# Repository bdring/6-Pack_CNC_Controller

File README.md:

# 6-Pack Grbl_ESP32 CNC Controller

### Overview

This is a fully modular CNC controller that runs Grbl_ESP32 firmware.

### Current Source Files.

The latest versions are [now on OSHLabs](https://oshwlab.com/bdring?tab=project&page=1) with the free version of EasyEDA. I did this to make it more accessible and easier to order.

### Features

- ESP32 Sockets to fit both narrow and wide 2 x 19 pin types.
- (6) Stepper Driver Outputs. These can be used for 6 axes (XYZABC) or any (2) can be ganged to allow dual motors on a single axis. These ganged motors can be controlled independently for axis squaring. It supports these types of drivers. Each driver has an independent enable/disable pin.
  - Standard Pololu/StepStick style driver modules.
  - Trinamic SPI type drivers. These are the ultra quiet types with sensorless endstop capability.
  - External Driver with 5V opto isolators.
(5) CNC I/O Modules. These interface with your machine. They include, but are not limited to, siwtch inputs, spindle control and accessory control. Currently there are (5) modules available.
  - High current AC/DC relay
  - 4x 5V Buffered output for lasers, PWM, spindle direction, spindle enable, ect.
  - RS485 Modbus Spindles
  - 0-10V Output Spindles
  - 4x Switch input with Optocouplers, filtering and Schmitt triggers. 
- SD Card Socket
- JTAG Programming/Debugging connector (or access to addition I/O pins

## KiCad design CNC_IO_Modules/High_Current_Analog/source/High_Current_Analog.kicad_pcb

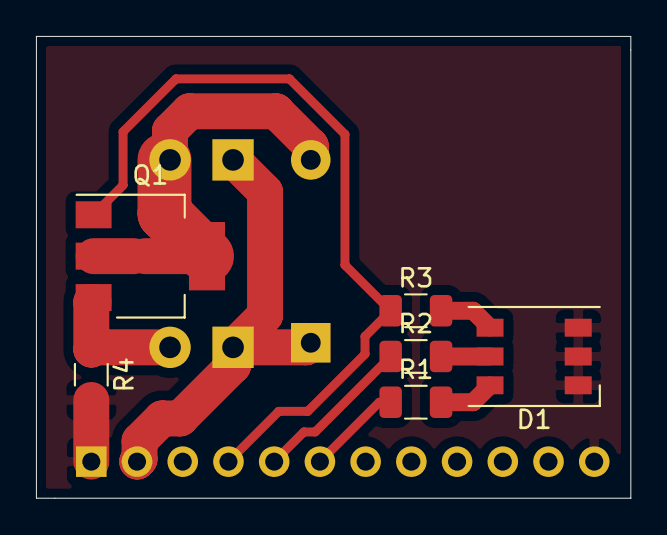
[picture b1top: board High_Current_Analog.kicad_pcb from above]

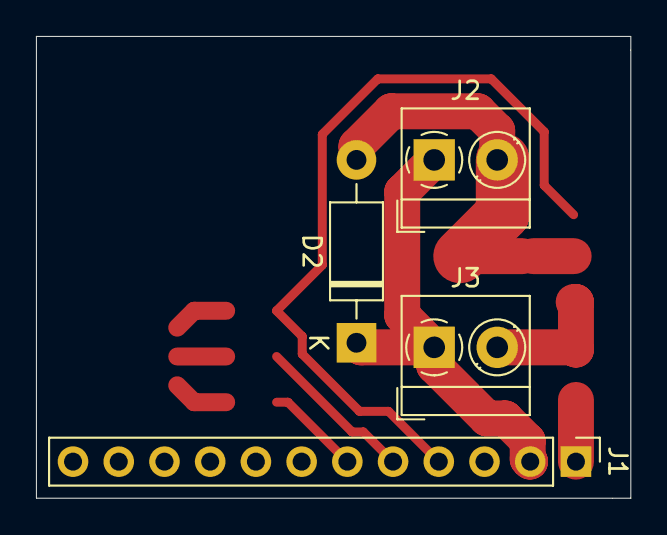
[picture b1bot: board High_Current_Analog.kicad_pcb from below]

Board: 2 copper layers, 33.0 x 25.7 mm, 10 parts (4 on the bottom side), 10 nets.

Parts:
D1: LED_RGB; LED_WS2812_PLCC6_5.0x5.0mm_P1.6mm
D2: 1N4003; D_DO-41_SOD81_P10.16mm_Horizontal
J1: Conn_01x12_Male; PinHeader_1x12_P2.54mm_Vertical
J2, J3: Screw_Terminal_01x02; TerminalBlock_MetzConnect_Type059_RT06302HBWC_1x02_P3.50mm_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
Q1: Q_NMOS_GDSD; SOT-223
R1, R2, R3, R4: R; R_1206_3216Metric

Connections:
GND: D1.1, D1.2, D1.3, J1.1, J1.12, R4.2
GNDPWR: J3.2, Q1.3, R4.1
IN1: J1.4, Q1.1, R3.1
IN2: J1.5, R2.1
IN3: J1.6, R1.1
unnamed: D1.4, R3.2
unnamed: D1.5, R2.2
unnamed: D1.6, R1.2
OUT1: D2.2, J2.2, Q1.2, Q1.4
VCC: D2.1, J1.2, J2.1, J3.1

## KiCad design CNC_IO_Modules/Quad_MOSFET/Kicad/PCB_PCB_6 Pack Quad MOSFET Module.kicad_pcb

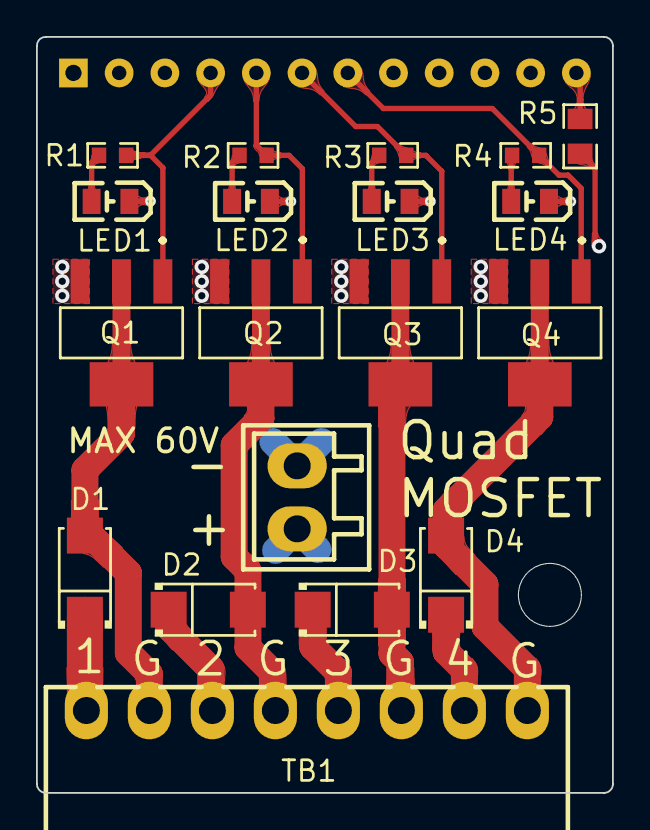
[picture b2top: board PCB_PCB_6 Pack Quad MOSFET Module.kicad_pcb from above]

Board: 2 copper layers, 32.0 x 42.0 mm, 20 parts (0 on the bottom side), 15 nets.

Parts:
D1, D2, D3, D4: B340A; SMA_L4.3-W2.6-LS5.2-RD
LED1, LED2, LED3, LED4: SZYY0805G; LED0805-R-RD
MOD1: 6 Pack Module Pins Bottom; 6 PACK MODULE PCB BOTTOM
Q1, Q2, Q3, Q4: NCE6005AR; SOT-223_L6.5-W3.5-P2.30-LS7.0-BR
R1, R2, R3, R4: 5.1kΩ; R0603
R5: 10MΩ; R0805
TB1: KF2EDGR-3.5-8P; CONN-TH_8P-P3.50_KF2EDGR-3.5-8P
TB2: KF2EDGV-3.5-2P; CONN-TH_P3.50_KF2EDGV-3.5-2P

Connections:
GND: LED1.2, LED2.2, LED3.2, LED4.2, MOD1.1, MOD1.12, R5.1
GND_VM: Q1.3, Q2.3, Q3.3, Q4.3, R5.2, TB2.2
LED1_1: LED1.1, R1.1
LED2_1: LED2.1, R2.1
LED3_1: LED3.1, R3.1
LED4_1: LED4.1, R4.1
MOD1_4: MOD1.4, Q1.1, R1.2
MOD1_5: MOD1.5, Q2.1, R2.2
MOD1_6: MOD1.6, Q3.1, R3.2
MOD1_7: MOD1.7, Q4.1, R4.2
Q1_2: D1.2, Q1.2, Q1.4, TB1.2
Q2_2: D2.2, Q2.2, Q2.4, TB1.4
Q3_2: D3.2, Q3.2, Q3.4, TB1.6
Q4_2: D4.2, Q4.2, Q4.4, TB1.8
VM: D1.1, D2.1, D3.1, D4.1, TB1.1, TB1.3, TB1.5, TB1.7, TB2.1

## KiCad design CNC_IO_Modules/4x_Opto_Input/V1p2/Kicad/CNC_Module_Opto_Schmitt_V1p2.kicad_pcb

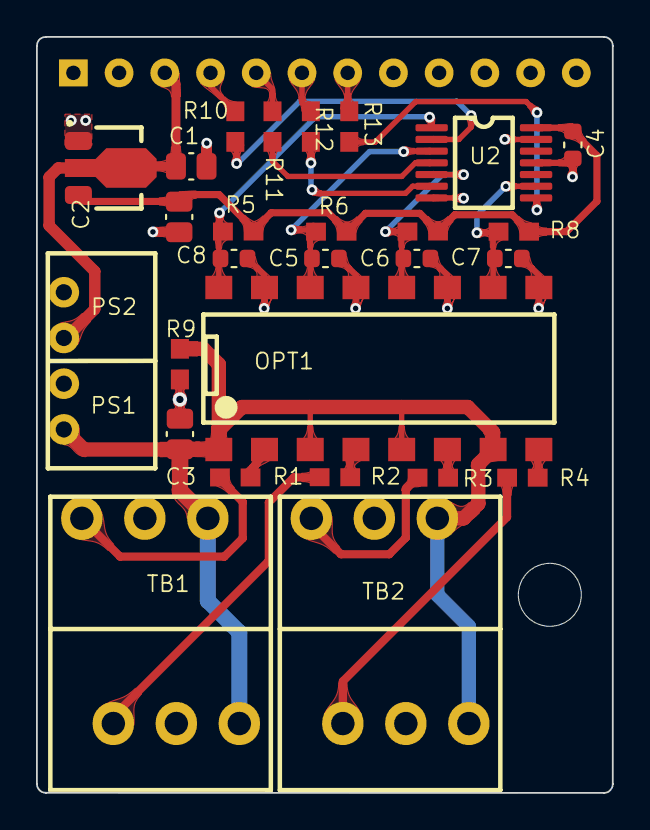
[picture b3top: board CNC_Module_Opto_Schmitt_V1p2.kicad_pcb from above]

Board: 2 copper layers, 32.0 x 42.0 mm, 28 parts (0 on the bottom side), 25 nets.

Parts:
C1, C2: 1uF; CAP_0805_N
C3: 2.2uF; CAP_0805_N_C3
C4: 100nF; CAP_0603_N
C5, C6, C7, C8: 100nF; CAP_0603_N_C5
MOD1: CNC_MODULE; CNC_Module_V3
OPT1: TP521-4; TLP521-4SM
PS1: 5V; B0505S-1WR3
PS2: 3.3V; SOT89
R1, R2, R3: 300R; RES_0603
R4: 300R; RES_0603_R4
R5: 10k; RES_0603_R5
R6: 10k; RES_0603_R6
R7: 10k; RES_0603_R7
R8: 10k; RES_0603_R8
R9: 220R; RES_0603_R9
R10: 220R; RES_0603_R10
R11: 220R; RES_0603
R12, R13: 220R; RES_0603_R12
TB1, TB2: KL128H-3.5_3X2; KF128-3.5-3x2
U2: SN74AC14D; TSSOP-14

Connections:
3v3: C2.1, C4.1, PS2.3, R5.1, R6.1, R7.1, R8.1, U2.14
5V: C1.1, MOD1.3, PS1.2, PS2.2
Gnd: C1.2, C2.2, C4.2, C5.1, C6.1, C7.1, C8.1, MOD1.1, MOD1.12, OPT1.9, OPT1.11, OPT1.13, OPT1.15, PS1.1, PS2.1, U2.7, U2.11, U2.13
Net_2: C3.1, OPT1.1, OPT1.3, OPT1.5, OPT1.7, PS1.4, R9.2, TB1.3, TB1.6, TB2.3, TB2.6
Net_3: OPT1.2, R1.2
Net_4: OPT1.4, R2.2
Net_5: OPT1.6, R3.2
Net_6: OPT1.8, R4.2
Net_8: C8.2, OPT1.16, R5.2, U2.1
Net_9: C5.2, OPT1.14, R6.2, U2.3
Net_11: C6.2, OPT1.12, R7.2, U2.5
Net_12: C7.2, OPT1.10, R8.2, U2.9
Net_13: R1.1, TB1.1
Net_14: R2.1, TB1.4
Net_15: R3.1, TB2.1
Net_16: R4.1, TB2.4
Net_17: MOD1.7, R13.1
Net_18: MOD1.4, R10.1
Net_19: MOD1.5, R11.1
Net_20: MOD1.6, R12.1
Net_21: R10.2, U2.2
Net_22: R11.2, U2.4
Net_23: R13.2, U2.8
Net_24: R12.2, U2.6
Net_31: C3.2, PS1.3, R9.1, TB1.2, TB1.5, TB2.2, TB2.5

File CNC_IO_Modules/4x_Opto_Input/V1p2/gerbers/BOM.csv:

"RefDes","Value","Name","Quantity","Manufacturer","MFG P/N"
"C1, C2","1uF","NP_1uF_50V_0805","2","CCTC","TCC0805X7R105K500DTB"
"C3","2.2uF","NP_2.2uF_16V_0805","1","Samsung Electro-Mechanics","CL21B225KOFNNNE"
"C4, C5, C6, C7, C8","100nF","NP_100nF_50V_0603","5","KEMET","C0603C104K5RACTU"
"MOD1","","CNC_Module","1","CJT(Changjiang Connectors)","A2541WV-12P"
"OPT1","TP521-4","TLP521-4","1","Isocom Components","TLP521-4GBSM"
"PS1","5V","B0505S-1WR3","1","MORNSUN Guangzhou S&T","B0505S-1WR3"
"PS2","3.3V","LDO_3V3_150mA_SOT-89","1","Diodes Incorporated","AP2204RA-3.3TRG1"
"R1, R2, R3, R4","300R","300R_0603","4","YAGEO","RC0603FR-07330RL"
"R5, R6, R7, R8","10k","10k_0603","4","YAGEO","RC0603FR-0710KL"
"R9, R10, R11, R12, R13","220R","220R_0603","5","YAGEO","RC0603FR-07220RL"
"TB1, TB2","","KL128H-3.5_3x2","2","KEFA","KF128A-3.5 3P"
"U2","","SN74AC14D","1","Texas Instruments","SN74HC14PWR"

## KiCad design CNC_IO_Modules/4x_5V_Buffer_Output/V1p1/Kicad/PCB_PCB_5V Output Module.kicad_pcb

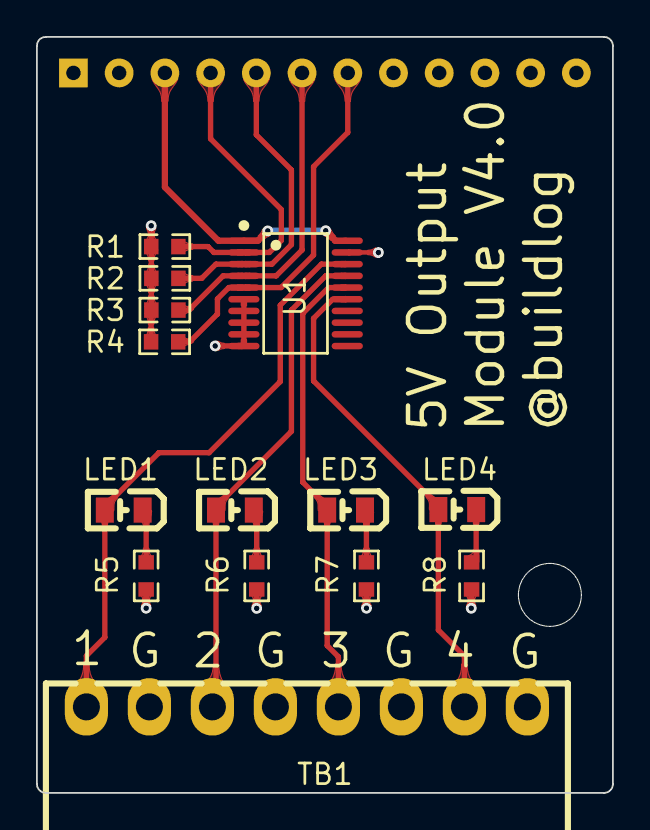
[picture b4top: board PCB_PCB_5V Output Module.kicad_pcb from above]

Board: 2 copper layers, 32.0 x 42.0 mm, 15 parts (0 on the bottom side), 14 nets.

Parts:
LED1, LED2, LED3, LED4: SZYY0805G; LED0805-R-RD
MOD1: 6 Pack Module Pins Bottom 3D; 6 PACK MODULE PCB BOTTOM_3D
R1, R2, R3, R4: 10kΩ; R0603
R5, R6, R7, R8: 5.1kΩ; R0603
TB1: KF2EDGR-3.5-8P; CONN-TH_8P-P3.50_KF2EDGR-3.5-8P
U1: MC74ACT245DTR2G; TSSOP-20_L6.5-W4.4-P0.65-LS6.4-BL

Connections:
+5V: MOD1.3, U1.1, U1.20
GND: MOD1.1, MOD1.12, R1.1, R2.1, R3.1, R4.1, R5.1, R6.1, R7.2, R8.2, TB1.2, TB1.4, TB1.6, TB1.8, U1.6, U1.7, U1.8, U1.9, U1.10, U1.19
LED1_2: LED1.2, R5.2
LED2_2: LED2.2, R6.2
LED3_2: LED3.2, R7.1
LED4_2: LED4.2, R8.1
OUT1: MOD1.4, R1.2, U1.2
OUT2: MOD1.5, R2.2, U1.3
OUT3: MOD1.6, R3.2, U1.4
OUT4: MOD1.7, R4.2, U1.5
U1_15: LED4.1, TB1.7, U1.15
U1_16: LED3.1, TB1.5, U1.16
U1_17: LED2.1, TB1.3, U1.17
U1_18: LED1.1, TB1.1, U1.18

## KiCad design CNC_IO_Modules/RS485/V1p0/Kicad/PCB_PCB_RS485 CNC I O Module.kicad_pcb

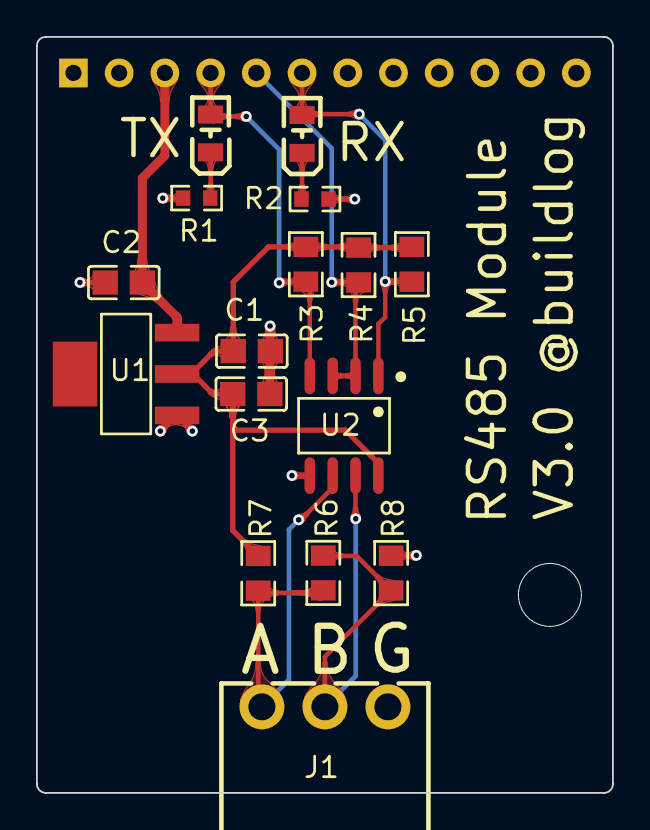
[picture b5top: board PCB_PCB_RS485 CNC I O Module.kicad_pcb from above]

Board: 2 copper layers, 32.0 x 42.0 mm, 17 parts (0 on the bottom side), 10 nets.

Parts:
C1, C2: 10uF; C0805
C3: 100nF; C0805
J1: KF2EDGR-3.5-3P; CONN-TH_3P-P3.50_KF2EDGR-3.5-3P
LED1, LED2: SZYY0805G; LED0805-R-RD
MOD1: 6 Pack Module Pins Bottom; 6 PACK MODULE PCB BOTTOM
R1, R2: 2kΩ; R0603
R3, R4, R5: 10kΩ; R0805
R6: 120Ω; R0805
R7, R8: 20kΩ; R0805
U1: AMS1117-3.3_C369933; SOT-223-4_L6.5-W3.5-P2.30-LS7.0-BR
U2: MAX3485ESA+T; SOIC-8_L4.9-W3.9-P1.27-LS6.0-BL

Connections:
+3V3: C1.2, C3.2, R3.2, R4.2, R5.2, R7.2, U1.2, U2.8
+5V: C2.2, MOD1.3, U1.3
GND: C1.1, C2.1, C3.1, J1.3, MOD1.1, MOD1.12, R1.1, R2.1, R8.1, U1.1, U2.5
MOD_CTRL: MOD1.5, R4.1, U2.2, U2.3
MOD_RX: LED2.1, MOD1.6, R5.1, U2.1
MOD_TX: LED1.1, MOD1.4, R3.1, U2.4
R1_2: LED1.2, R1.2
R2_2: LED2.2, R2.2
U2_6: J1.1, R6.2, R7.1, U2.6
U2_7: J1.2, R6.1, R8.2, U2.7

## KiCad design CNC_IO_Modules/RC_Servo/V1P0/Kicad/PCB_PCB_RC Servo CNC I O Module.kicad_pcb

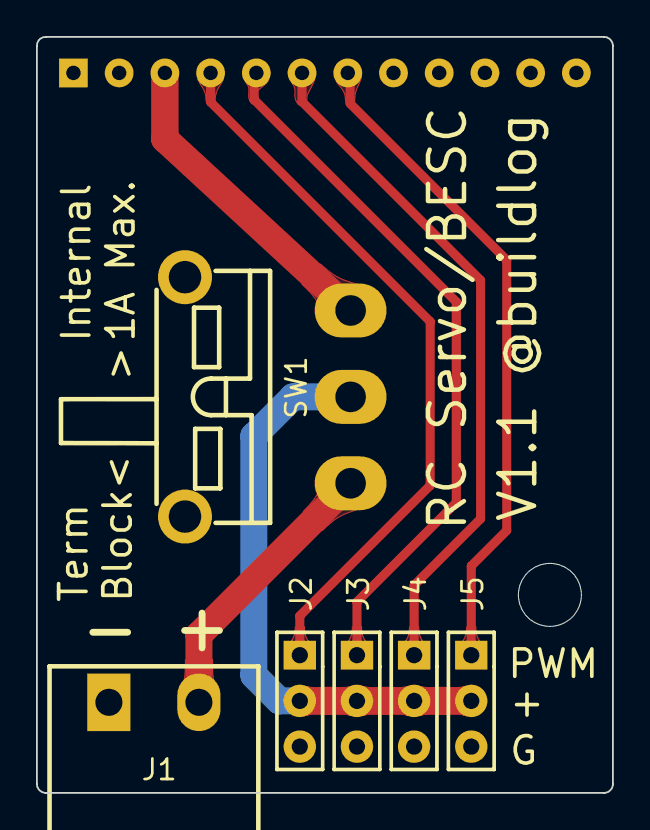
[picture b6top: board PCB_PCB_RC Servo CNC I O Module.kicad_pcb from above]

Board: 2 copper layers, 32.0 x 42.0 mm, 7 parts (0 on the bottom side), 8 nets.

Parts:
J1: XY2500R-B-5.00-2P; CONN-TH_2P-P5.00_XY2500R-B-5.00-2P
J2, J3, J4, J5: Header-Male-2.54_1x3; HDR-TH_3P-P2.54-V-M-1
MOD1: 6 Pack Module Pins Bottom; 6 PACK MODULE PCB BOTTOM
SW1: SS-12D11G5; SW-TH_SS-12D11G5

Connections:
+5V: MOD1.3, SW1.3
GND: J1.1, J2.3, J3.3, J4.3, J5.3, MOD1.1, MOD1.12
OUT1: J2.1, MOD1.4
OUT2: J3.1, MOD1.5
OUT3: J4.1, MOD1.6
OUT4: J5.1, MOD1.7
V_EXT: J1.2, SW1.1
V_SERVO: J2.2, J3.2, J4.2, J5.2, SW1.2

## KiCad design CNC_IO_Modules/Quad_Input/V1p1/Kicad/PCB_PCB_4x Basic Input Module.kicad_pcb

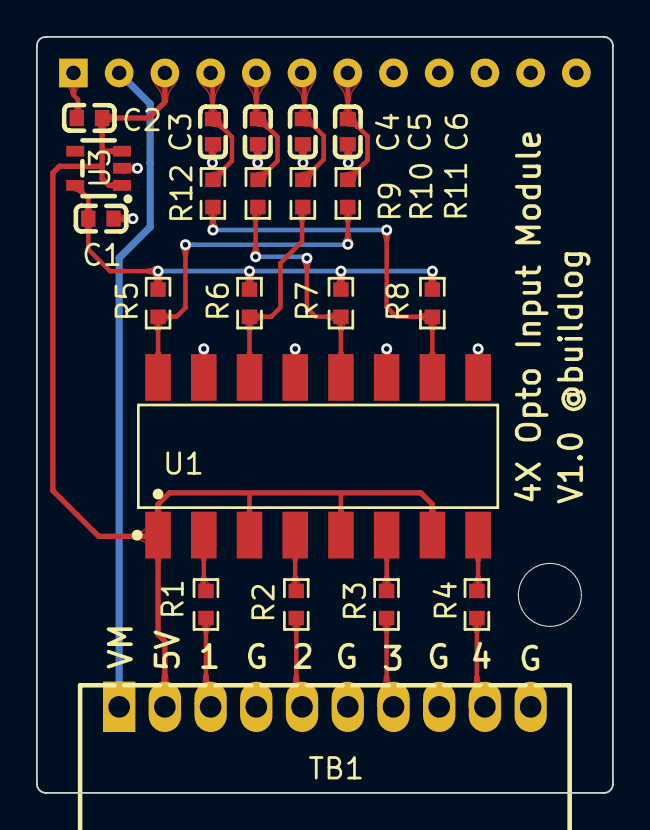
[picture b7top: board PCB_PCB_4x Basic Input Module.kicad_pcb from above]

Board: 2 copper layers, 32.0 x 42.0 mm, 22 parts (0 on the bottom side), 20 nets.

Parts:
C1, C2: 1uF; C0603
C3, C4, C5, C6: 100nF; C0603
MOD1: 6 Pack Module Pins Bottom 3D; 6 PACK MODULE PCB BOTTOM_3D
R1, R2, R3, R4: 300Ω; R0603
R5, R6, R7, R8: 10kΩ; R0603
R9, R10, R11, R12: 1kΩ; R0603
TB1: KF2EDGR-2.54-10P; CONN-TH_10P-P2.54_KF2EDGR-2.54-10P
U1: TLP521-4XSM; SMD-16_L20.0-W6.5-P2.54-LS10.2-BL
U3: LP5907MFX-3.3/NOPB; SOT-23-5_L3.0-W1.7-P0.95-LS2.8-BR

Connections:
+3V3: C1.2, R5.2, R6.2, R7.2, R8.2, U3.5
+5V: C2.2, MOD1.3, TB1.2, U1.1, U1.3, U1.5, U1.7, U3.1, U3.3
GND: C1.1, C2.1, C3.1, C4.1, C5.1, C6.1, MOD1.1, MOD1.12, TB1.4, TB1.6, TB1.8, TB1.10, U1.9, U1.11, U1.13, U1.15, U3.2
INPUT1: C6.2, MOD1.7, R11.2
INPUT2: C5.2, MOD1.6, R10.2
INPUT3: C4.2, MOD1.5, R9.2
INPUT4: C3.2, MOD1.4, R12.2
TB1_3: R1.1, TB1.3
TB1_5: R2.1, TB1.5
TB1_7: R3.1, TB1.7
TB1_9: R4.1, TB1.9
U1_2: R1.2, U1.2
U1_4: R2.2, U1.4
U1_6: R3.2, U1.6
U1_8: R4.2, U1.8
U1_10: R8.1, R12.1, U1.10
U1_12: R7.1, R9.1, U1.12
U1_14: R6.1, R10.1, U1.14
U1_16: R5.1, R11.1, U1.16
VMOT: MOD1.2, TB1.1

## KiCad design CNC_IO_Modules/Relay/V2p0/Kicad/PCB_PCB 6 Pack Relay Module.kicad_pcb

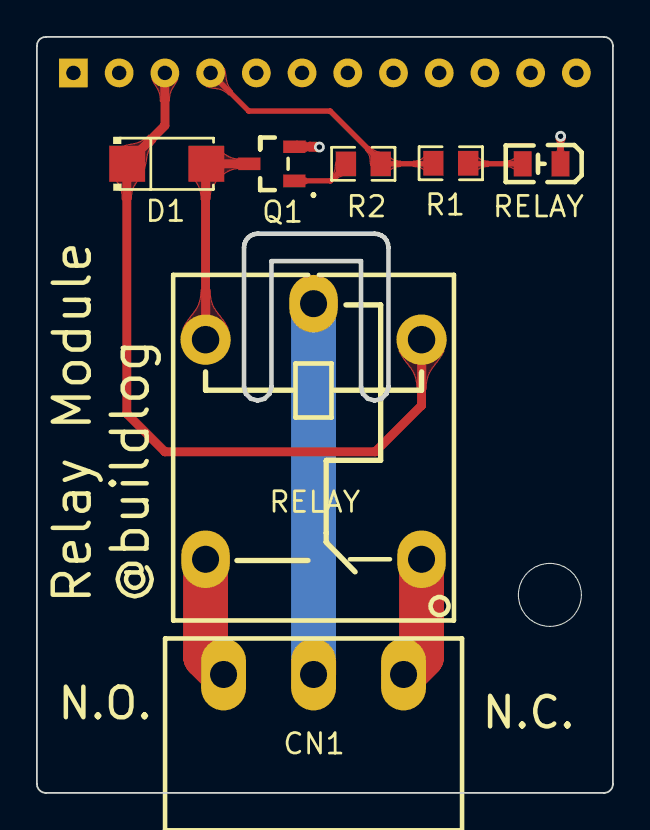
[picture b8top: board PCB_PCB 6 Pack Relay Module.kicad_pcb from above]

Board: 2 copper layers, 31.8 x 41.8 mm, 8 parts (0 on the bottom side), 9 nets.

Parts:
CN1: XY2500R-B-5.00-3P; CONN-TH_XY2500R-B-5.00-3P
D1: B340A; SMA_L4.3-W2.6-LS5.2-RD
MOD1: 6 Pack Module Pins Bottom 3D; 6 PACK MODULE PCB BOTTOM_3D
Q1: MMBT9014B; TO-236-3_L2.9-W1.3-P1.90-LS2.4-BR
R1: 2kΩ; R0805
R2: 1kΩ; R0805
RELAY: SZYY0805G; LED0805-R-RD
RELAY#2: SRD-05VDC-SL-C; RELAY-TH_SRD-XXVDC-XL-C

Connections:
+5V: D1.1, MOD1.3, RELAY#2.4
GND: MOD1.1, MOD1.12, Q1.2, RELAY.2
Q1_1: Q1.1, R2.2
R1_1: R1.1, RELAY.1
R2_1: MOD1.4, R1.2, R2.1
RLY1_1: D1.2, Q1.3, RELAY#2.1
RLY1_2: CN1.1, RELAY#2.2
RLY1_3: CN1.3, RELAY#2.3
RLY1_5: CN1.2, RELAY#2.5

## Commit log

2020-05-29 First Push
2020-05-29 Add photo
2020-06-27 Uploading V1p0
2020-06-27 moved schematic
2020-07-12 Added CNC I/O Modules
2020-07-12 Added image
2020-07-12 Add relay module image
2020-07-14 Added version 1p1
2020-07-15 Adding schemaic PDF
2020-07-25 Updating modules and adding external driver adapter
2020-08-07 Adding 3D files for module supports.
    The modules are typically supported on the outside edge with a single 11mm threaded spacer. That works OK, but I designed 2 3D parts that provide a little extra support.
2020-08-10 Update 5V Output module
    - Fix some BOM issues
2020-08-19 Added machine_defs folder. Will put examples in here.
2020-08-21 3D part and new machine def
2020-08-26 adding more machine defs
2020-08-27 Added terminal blocks to BOM
2020-09-03 more def examples
2020-09-14 Added V1p5 source files
2020-09-14 Added v1p2 of opto input module
2020-09-14 Added V2p0 of relay module
2020-09-14 Added Quad Mosfet files
2020-09-17 Adding more files
2020-09-21 adding step file
2020-09-22 new machine def
2020-09-24 Updated machine defs and added readme.
2020-09-29 Added case files
2020-10-04 Updates to case and machine defs
2020-10-10 Added machine defs and RC Servo Module
2020-10-17 new machine defs
2020-10-17 Update machine def comments
2020-11-04 Added machine defs
2020-11-06 Addede more user machine definitions
2020-11-11 More machine defs
2020-12-14 Add a new module
2020-12-16 New module and machine defs
2020-12-27 Adding ne machine defs
2021-01-23 Adding machine defs
2021-02-26 Adding machine definitions
2021-03-19 adding defs
2021-04-02 Added version 1.8 files
2021-04-02 added sd files
2021-04-06 adding files
2021-04-21 More defs
2021-05-18 Updates to machine defs
2021-06-24 Update 6_pack_external_XYYZ_10vSpin_Mist_Flood_Relays.h
    Fix typo in Y@ disable
2021-06-28 Updating 3D files
2021-08-02 New machine definitions
2021-08-20 more mach defs
2021-12-22 Adding configs
2022-02-03 configs
2022-03-22 Updated parts
2022-04-09 adding
2022-04-28 adding cfgs
2022-06-11 config updates
2022-07-25 add files
2022-09-04 Add template footrpint and symbol
    A base template for 6 pack expansion modules in Kicad
2022-09-13 Add Kicad versions
2022-11-14 update configs
2023-04-07 add configs
2023-06-09 Adding config
